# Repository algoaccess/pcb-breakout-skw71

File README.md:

# pcb-breakout-skw71
Pin breakout of the Skylab SKW71 AR9331-based module to through-hole pin headers for prototyping.

##PCB Design software and addons used

1. Eagle 7.5.0: I use Standard but Light should still be able to open/modify the files.
2. SKW71 library by [DIY modules](https://github.com/baseapp/EagleLibrary) (in repo as BaseApp.lbr)

##Images

None yet

##Schematic drawings
Images are exported from Eagle at 600dpi.

##Parts required

1. SKW71 Module which can be bought from Aliexpress [here](http://www.aliexpress.com/store/product/Skylab-Access-Point-WiFi-modules-SKW71-WIFI-Module-Integrates-internal-AP-and-LNA-Client-Repeater-10pcs/100058_2003437490.html)
2. 20-pin, 2-row, 1.27mm pitch receptacle like [this](http://sg.element14.com/samtec/fle-120-01-g-dv/product-range-fle-series/dp/1667674)

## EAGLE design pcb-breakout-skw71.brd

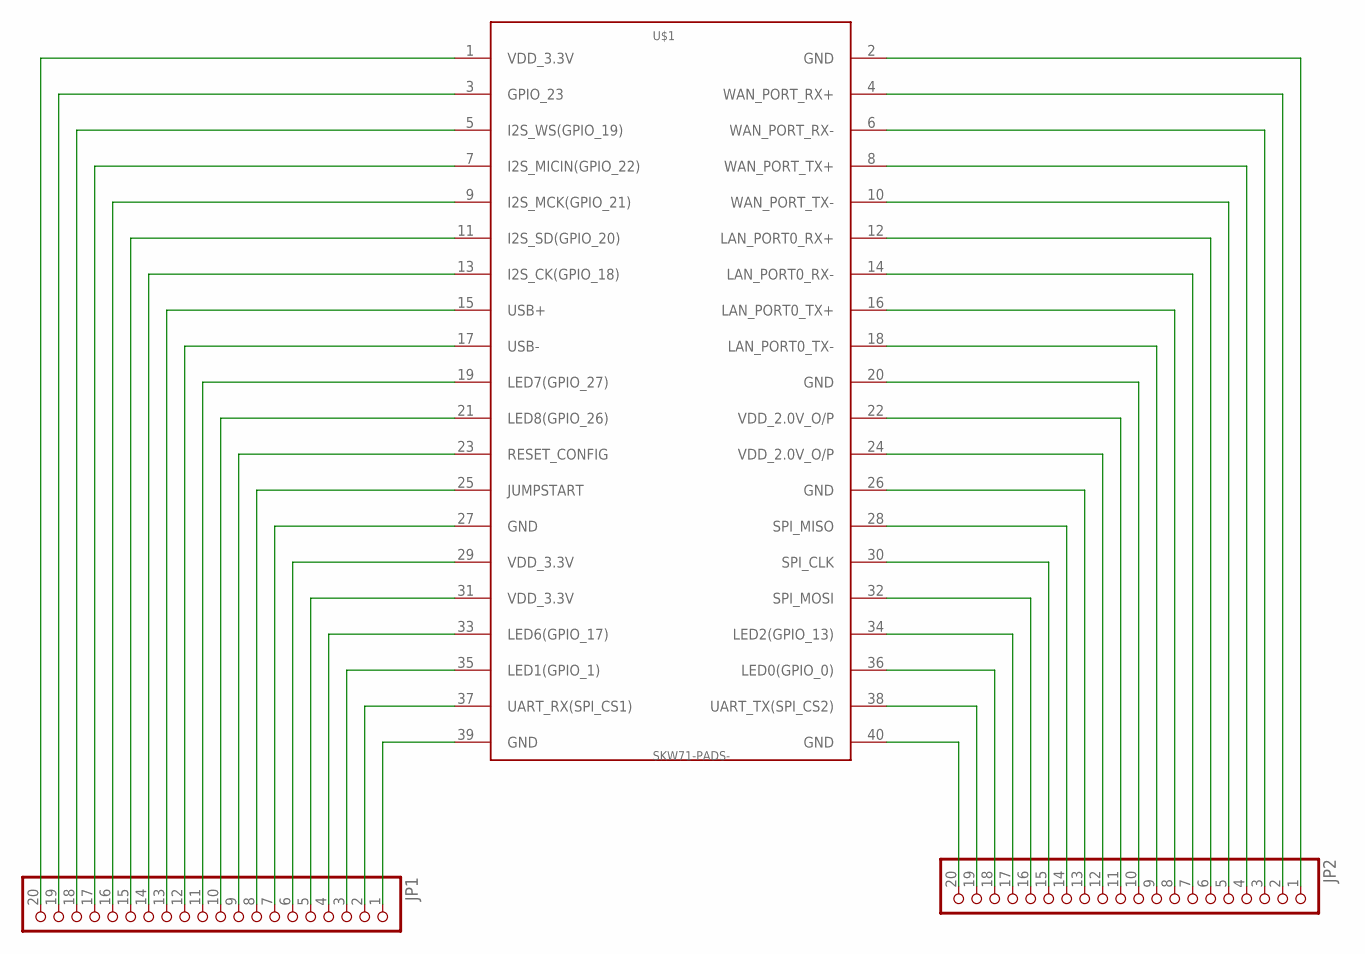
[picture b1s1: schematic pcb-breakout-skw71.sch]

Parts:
JP1, JP2: PINHD-1X20; 1X20
U$1: SKW71-PADS-; SKW71-SMT

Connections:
unnamed: JP1.20, U$1.1 (VDD_3.3V)
unnamed: JP2.1, U$1.2 (GND)
unnamed: JP1.18, U$1.5 (I2S_WS(GPIO_19))
unnamed: JP1.19, U$1.3 (GPIO_23)
unnamed: JP2.2, U$1.4 (WAN_PORT_RX+)
unnamed: JP1.17, U$1.7 (I2S_MICIN(GPIO_22))
unnamed: JP1.16, U$1.9 (I2S_MCK(GPIO_21))
unnamed: JP1.15, U$1.11 (I2S_SD(GPIO_20))
unnamed: JP1.14, U$1.13 (I2S_CK(GPIO_18))
unnamed: JP1.13, U$1.15 (USB+)
unnamed: JP1.12, U$1.17 (USB-)
unnamed: JP1.11, U$1.19 (LED7(GPIO_27))
unnamed: JP1.10, U$1.21 (LED8(GPIO_26))
unnamed: JP1.9, U$1.23 (RESET_CONFIG)
unnamed: JP1.8, U$1.25 (JUMPSTART)
unnamed: JP1.7, U$1.27 (GND)
unnamed: JP1.6, U$1.29 (VDD_3.3V)
unnamed: JP1.5, U$1.31 (VDD_3.3V)
unnamed: JP1.4, U$1.33 (LED6(GPIO_17))
unnamed: JP1.3, U$1.35 (LED1(GPIO_1))
unnamed: JP1.2, U$1.37 (UART_RX(SPI_CS1))
unnamed: JP1.1, U$1.39 (GND)
unnamed: JP2.3, U$1.6 (WAN_PORT_RX-)
unnamed: JP2.4, U$1.8 (WAN_PORT_TX+)
unnamed: JP2.5, U$1.10 (WAN_PORT_TX-)
unnamed: JP2.6, U$1.12 (LAN_PORT0_RX+)
unnamed: JP2.7, U$1.14 (LAN_PORT0_RX-)
unnamed: JP2.8, U$1.16 (LAN_PORT0_TX+)
unnamed: JP2.9, U$1.18 (LAN_PORT0_TX-)
unnamed: JP2.10, U$1.20 (GND)
unnamed: JP2.11, U$1.22 (VDD_2.0V_O/P)
unnamed: JP2.12, U$1.24 (VDD_2.0V_O/P)
unnamed: JP2.13, U$1.26 (GND)
unnamed: JP2.14, U$1.28 (SPI_MISO)
unnamed: JP2.15, U$1.30 (SPI_CLK)
unnamed: JP2.16, U$1.32 (SPI_MOSI)
unnamed: JP2.17, U$1.34 (LED2(GPIO_13))
unnamed: JP2.18, U$1.36 (LED0(GPIO_0))
unnamed: JP2.19, U$1.38 (UART_TX(SPI_CS2))
unnamed: JP2.20, U$1.40 (GND)

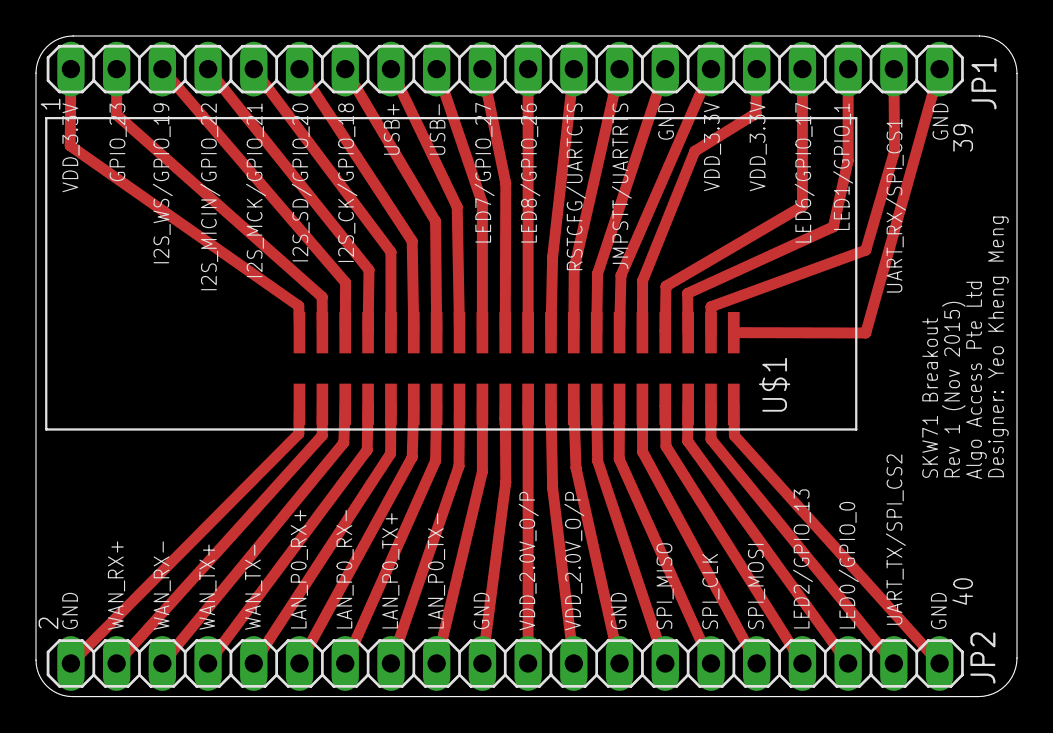
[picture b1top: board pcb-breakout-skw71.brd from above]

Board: 2 copper layers, 54.5 x 36.7 mm, 3 parts (0 on the bottom side), 40 nets.

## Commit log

2015-11-18 lck file in gitignore
2015-11-18 silkscreen changes
2015-11-18 make schematic smaller
2015-11-18 images and gerbel
